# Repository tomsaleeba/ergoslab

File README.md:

> a columnar stagged keyboard that uses a combination of Cherry MX (or
> compatible) and Kailh choc switches to pack in a heap of thumb keys

*Update Dec 2020*: I've been using this keyboard full time (I'm a professional
software developer so it sees a lot of use) for a year now and I'm still in love
with it. If you're considering making one, I would call this design battle
proven now.

*Update Jan 2022*: Still using this full-time and loving it 💪.

- [What is this thing?](#what-is-this-thing)
- [Desgin choices:](#desgin-choices)
- [Build guide](#build-guide)
- [Gerbers](#gerbers)
- [Parts list](#parts-list)
  * [Parts you'll have to find yourself](#parts-youll-have-to-find-yourself)
  * [Parts available with PCB order](#parts-available-with-pcb-order)
- [Developers/contributing](#developerscontributing)
  * [Generating 3 layers of sandwich case](#generating-3-layers-of-sandwich-case)
  * [Generating gerbers](#generating-gerbers)
- [Credit for Kicad symbols/footprints](#credit-for-kicad-symbolsfootprints)
- [FAQ](#faq)

# What is this thing?
Before swapping to this keyboard, I had been using an ErgoDox Infinity and an EZ
as my daily drivers for quite a few years. I loved using them but I was looking
for something more compact and with more (easily accessible) thumb keys. There
are so many candidates
([here](https://docs.google.com/spreadsheets/d/19-rTWbp8SCKdZFByPZu3RT8NSF8vVddDe8WL6R6b1qQ/edit?usp=sharing),
[here](https://keebfol.io/), [here](https://golem.hu/boards/) and
[here](https://github.com/diimdeep/awesome-split-keyboards)) but none match
*exactly* what I want, so I decided build my own!

# Desgin choices:
  - Kailh hotswap sockets for all the MX-style switches (choc are soldered in)
  - ErgoDox style ortho-columnar but with the extra little finger offset of the
      [Diverge 3](https://unikeyboard.io/product/diverge-3/)
  - Make all thumb keys easily accessible from the normal hand position
  - keys for vim-style arrows on the right hand, and directly below the home row
  - same plate design for both halves
  - compatible with QMK firmware, see [keyboard directory in QMK](https://github.com/qmk/qmk_firmware/tree/master/keyboards/ergoslab)
  - optional top LED for layer status ([example](./misc/layer-led-in-action.jpg))
  - optional underglow LEDs
  - minimise overall footprint by using internal standoffs (thanks for the idea
      [ErgoTravel](https://github.com/jpconstantineau/ErgoTravel))
  - use only 1U key caps to minimise size and because stabilisers are annoying
  - author a single "master" PCB and use a python script to generate the 3
      layers of the sandwich case. Makes life much easier to keep them all in
      sync. (See further down for more info)
  - support 5-pin/PCB mount switches

# Build guide
See the [guide here](./build-guide.md).

# Gerbers
See the [releases](https://github.com/tomsaleeba/ergoslab/releases) for this
GitHub repo for the generated Gerber files. You probably want the most recent
version.

If you need to generate your own gerbers, see [how to turn the master PCB into
the 3 generated PCBs](#generating-3-layers-of-sandwich-case) and then [how to
generate gerbers](#generating-gerbers).

# Parts list
## Parts you'll have to find yourself
  - 2x top PCBs (optional if you're happy with PCB mount; untested)
  - 2x middle PCBs (or 4x as they can also be used as the base)
  - 2x base PCBs (if you didn't order 4x middle)
  - 2x Pro Micros
  - 1x TRRS cable
  - 42x Cherry MX (or compatible) switches
  - 42x [Kailh hotswap PCB sockets](https://www.kailhswitch.com/mechanical-keyboard-switches/box-switches/mechanical-keyboard-switches-kailh-pcb-socket.html)
  - 10x Kailh choc switches
  - 42x 1U MX key caps
  - 10x 1U Kailh choc key caps
  - (optional) 2x WS2812 LED from a 144 LEDs/m strip, for layer status lights
  - (optional) more WS2812 LEDs, of any density per meter strip, for underglow
      lighting. 12x is probably a sane number but if you want to run them at
      lower power, you could probably use more.
  - 4x 15mm M2 standoffs (2 per side), for mounting the OLED/ProMicro acrylic cover
  - 8x M2 screws, between 4 and 8mm long, for the above standoffs
  - (optional) 1 or 2 OLED screens
  - 36x M2x4 screw (See Note1 and Note2) for mounting the middle/PCB layer to the base
      plate

**Note1**: the screw/bolt length depends on the height of the standoffs you get.
You want 1.6mm thick PCBs so make sure you don't have *too much* thread on your
screws.

**Note2**: it's highly recommended to get hex head/allen key/ISO7380 screws (see
image below). This is because a phillips head screwdriver probably won't fit
through the holes in the switch plate to tighten the screws on the middle/PCB
layer. You can always drill those holes a bit bigger or loctite the screws in
(so they won't need tighening) to workaround this. As you have hotswap sockets,
you may be able to remove the switches and pull the middle/PCB layer screws out
through the switch holes.  Beware: with 4mm long screws, I couldn't achieve
this, though it was very close.

## Parts available with PCB order
These are the parts you can order from LCSC at the same time as having your PCBs
manufactured. The listed quantity is to assemble *both halves*.

| QTY |  Description                       |  LCSC Part No |
| :---: | :--- | :---: |
|0/2/4| 4.7KO (4701) ±1% (2 per OLED)      |  [C58678](https://lcsc.com/product-detail/Metal-Film-Resistor-TH_4-7KR-4701-1_C58678.html) |
| 2  |  PJ-3200B-4A TRRS Connector         |  [C136687](https://lcsc.com/product-detail/Audio-Video-Connectors_Korean-Hroparts-Elec-PJ-3200B-4A_C136687.html) |
| 2  |  Switch 5.2*5.2*1.5 reset switch    |  [C92584](https://lcsc.com/product-detail/Tactile-Switches_Switch-5-2-5-2-1-5-250gf-Copper-head_C92584.html) |
| 2  |  2.54mm 1*40P round Female header   |  [C9811](https://lcsc.com/product-detail/Female-Header_2-54mm-1-40P-round-Female-header_C9811.html) |
|0/1/2|  OLED Female header                |  [C124413](https://lcsc.com/product-detail/Pin-Header-Female-Header_Ckmtw-Shenzhen-Cankemeng-C124413_C124413.html) |
| 52 |  1N4148 Switching Diode             |  [C14516](https://lcsc.com/product-detail/Switching-Diode_1N4148_C14516.html) |
| 18 |  M2x6mm standoffs (See Note3) for middle/PCB layer to base plate mounting |  [M2x6](https://lcsc.com/product-detail/Studs_Made-in-China-Made-in-China-M2-6-3-5_C193468.html) |

**Note3**: the standoffs between the middle/PCB layer and the base plate can be
quite small, probably as small as 3mm. The problem with that is making sure the
bolts engage the threads enough. Feel free to experiment with getting a super
slim keyboard. Perhaps use a long bolt, a threadless spacer and a nut?

# Developers/contributing
Contributions are welcome. I'm not selling these keyboards and I already have
two for myself so I can't afford to manfacture more PCBs to test changes. If you
make changes to the PCB design, ideally you would confirm it all works by
manufacturing your own PCBs.

Steps for contributing:

1. if it's a non-trival change, consider opening an issue on this repo to talk
   about the change before spending effort
1. fork this repo
1. make your changes
1. if you made a change to the PCB, you need to [regenerate the 3 seperate
   generated PCBs](#generating-3-layers-of-sandwich-case)
1. send a pull request

## Generating 3 layers of sandwich case
We edit a single PCB file that contains the information required to generate all
3 layers (switch plate, circuitry, base) of a sandwich case keyboard. Keeping it
all in one file ensures that things like mounting holes always stay lined up.

There is some magic in the settings of items on the PCB to indicate what layer
they belong on. Read the code for the specifics but as a general guide:
  - we use Eco1.User as the templates for edge cuts that only appear on some
      layers
  - the width of the drawing lines are slightly different so we can determine
      which belongs on each layer
  - the thickness of text is slightly different so we can determine which
      belongs on each layer

You *must* have Kicad installed in your system. Doing this makes the `pcbnew`
python module available. Make sure you don't have any virtualenv, etc activated
as you need to be using you system-wide python. Check for the module by running
the following in the python REPL:

```python
import pcbnew
```

Now you can regenerate the PCBs with:

```bash
python ./generate_pcbs.py
```

Normally keeping generated things in source control is not a good idea but in
the interest of keeping things easy, we include the generated PCBs.

## Generating gerbers
Using KiCad 5.1.4, here's the settings to generate gerbers.

Plot settings (should be the defaults):
```
Plot format: Gerber
Included layers:
  F.Cu
  B.Cu
  F.Paste
  B.Paste
  F.SilkS
  B.SilkS
  F.Mask
  B.Mask
  Edge.Cuts
Plot foorprint values: yes
Plot footprint references: yes
Exclude PCB edge layer from other layers: yes
Exclude pads from silkscreen: yes
Default line width: 0.1mm
Coordinate format: 4.6, unit mm
```

Drill settings:
```
Drill File Format: Excellon
Mirror Y axis: no
Minimal header: no
PTH and NPTH in single file: no
Oval Holes Drill Mode: Use alternate drill mode
Map File Format: PostScript
Drill Origin: Absolute
Drill Units: Inches
Zeros Format: Suppress leading zeros
```

The fix for the JLCPCB PTH layer error was to change the [oval hole drill
mode](https://forum.kicad.info/t/jlcpcb-gives-me-warnings-on-drill-and-edge-cuts/17565/25).

# Credit for Kicad symbols/footprints
- [Kailh reversible footprints](https://github.com/daprice/keyswitches.pretty/blob/f89ef994a51043281f3fa6dfb4a93d8e4bebdbd1/Kailh_socket_reversible.kicad_mod) ([CC BY-SA](https://github.com/daprice/keyswitches.pretty/blob/f89ef994a51043281f3fa6dfb4a93d8e4bebdbd1/LICENSE.md))
- [P-08073 TACT reset switch footprint](https://github.com/kata0510/minisplit/blob/5fc4b23/minisplit-footprint.pretty/TACT_SWITCH_TVBP06.kicad_mod) ([MIT License](https://github.com/kata0510/minisplit/blob/5fc4b233df8120694ade5a3a812970439e8fc585/LICENSE))
- [symbols: TRRS jack, resistor](https://github.com/MakotoKurauchi/helix/tree/master/PCB/beta) (exported from schematic) ([MIT License](https://github.com/MakotoKurauchi/helix/blob/master/LICENSE))
- [LED symbol](https://github.com/tmk/kicad_lib_tmk) (no license)
- 2.54mm pin headers and diode footprints from built in Kicad library
- [footprints: 4 pin TACT reset, ProMicro, diode](https://github.com/jpconstantineau/ErgoTravel/tree/d443bf4/Library/footprints.pretty) ([MIT License](https://github.com/jpconstantineau/ErgoTravel/blob/master/LICENSE))

# FAQ
**How portable is it?**
It weighs 360grams (180grams for each half) with cheap DSA plastic keycaps. It
measures 115mm x 102mm and with 6mm standoffs, it's 16mm to the top of the
switch plate or 31mm to the top of DSA keycaps, including the height of rubber
bump-ons. I'll let you decide how portable you think that is but it was designed
to be portable.

**Is I2C between the halves supported?**
Sort of. The OLED screens use I2C so you won't be able to use them. Also there's
no solder jumpers so you'll have to jump some wires between the OLED header
SDA/SCL pins and the SLAVE_LED pin/data pin on the unused TRRS jack. This isn't
an intended use but you can certainly hack it, check the schematic for details.

**What happened to a single PCB that works as all 3 layers?**
Originally I tried to make one PCB design that works as all 3 layers of a
sandwich design: base, PCB and switch plate. The idea was taken from
[for-split-keyboard](https://github.com/peej/for-split-keyboard) and
[mitosis](https://www.reddit.com/r/MechanicalKeyboards/comments/66588f/wireless_split_qmk_mitosis/).
I failed because I wanted to have minimal post-manufacture cutting by hand and
JLCPCB kept rejecting my desgins as they didn't have strong enough supports to
hold the PCB together though the whole manufacture process. So now we have
"master" PCB design and use a python script to generate the PCBs for each layer
from that master.

**Do you have keyboard-layout-editor source?**\
Yes. Either [this file](./layout.kle) in this repo or here's a (hopefully up to date)
<a href="http://www.keyboard-layout-editor.com/##@@_x:3&t=#000000%0A%0A#115219;&=E%0A%0A#&_x:9.75&t=#000000%0A%0A#115219%0A#9914a6;&=I%0A%0A*%0A%7D;&@_y:-0.875&x:2&t=#000000%0A%0A#115219;&=W%0A%0A/@&_x:1;&=R%0A%0A$&_x:7.75&t=#000000%0A%0A#115219%0A#9914a6;&=U%0A%0A/&%0A%7B&_x:1&t=#000000%0A%0A#115219;&=O%0A%0A';&@_y:-0.875&x:5;&=T%0A%0A%25&_x:5.75;&=Y%0A%0A%5E;&@_y:-0.625&x:1;&=Q%0A%0A!&_x:13.75;&=P%0A%0A%22;&@_y:-0.625&x:3;&=D%0A%0A3&_x:9.75&t=#000000%0A%0A#115219%0A#9914a6;&=K%0A%0A8%0A);&@_y:-0.875&x:2&t=#000000%0A%0A#115219;&=S%0A%0A2&_x:1;&=F%0A%0A4&_x:7.75&t=#000000%0A%0A#115219%0A#9914a6;&=J%0A%0A7%0A(&_x:1&t=#000000%0A%0A#115219;&=L%0A%0A9;&@_y:-0.875&x:5;&=G%0A%0A5&_x:5.75;&=H%0A%0A6;&@_y:-0.625&x:1;&=A%0A%0A1&_x:13.75;&=/:%0A/;%0A0;&@_y:-0.625&x:3&t=#000000%0A#0b458a%0A#115219;&=C%0A%0A+&_x:9.75&t=#000000%0A%0A#115219%0A#9914a6;&=%3C%0A,%0A%0A%5D;&@_y:-0.875&x:2&t=#000000%0A#0b458a%0A#115219;&=X%0A%0A-&_x:1;&=V%0A%0A/=&_x:7.75&t=#000000%0A%0A#115219%0A#9914a6;&=M%0A%0A~%0A%5B&_x:1&t=#000000;&=%3E%0A.;&@_y:-0.875&x:5&t=#000000%0A%0A#115219;&=B%0A%0A%60&_x:5.75;&=N%0A%0A/:;&@_y:-0.625&x:1&t=#000000%0A#0b458a%0A#115219;&=Z%0A%0A/_&_x:13.75&t=#000000;&=?%0A//;&@_y:-0.625&x:3;&=Del&_x:9.75&t=#000000%0A%0A%0A#9914a6;&=%0A%0A%0A%3E%0A%0A%0A%0A%0A%0A%E2%86%93;&@_y:-0.875&x:2&t=#000000;&=Alt&_x:1;&=GUI%0AEnter&_x:7.75&t=#000000%0A%0A%0A#9914a6;&=%0A%0A%0A%3C%0A%0A%0A%0A%0A%0A%E2%86%90&_x:1&t=#000000&a:7;&=%E2%86%91;&@_y:-0.875&x:5&a:4;&=Shift&=Ctrl&_x:3.75&t=#115219;&=Numb%0AEnter&_t=#000000;&=Space;&@_y:-0.625&x:1;&=Leader&_x:13.75&a:7;&=%E2%86%92;&@_y:-0.375&x:2;&=&_a:4;&=Swap&_t=#000000%0A#0b458a;&=Esc&_t=#ab0202;&=Media&_t=#9914a6;&=Brkt&_x:3.75&t=#000000;&=Tab&=AltTab&=Bspc&=Swap&_a:7;&=">permalink</a>

**Do you have a vector of the right hand "plate"?**\
Yep, see [misc/ergoslab-right.svg](misc/ergoslab-right.svg).

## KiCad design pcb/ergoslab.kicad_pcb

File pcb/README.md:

# What is this?
I'm learning about PCB design, so I can make my own mechanical keyboard. This
is a "hello world" project to test my ideas/goals.

# Goals
- Support for Kailh hotswap sockets (and kailh choc as solder on)
- add thumb keys, actually all keys, are accessible from the "home" hand
    position
- One PCB design that works as all 3 layers of a sandwich design: base, PCB and
    switch plate. Idea taken from [for-split-keyboard](https://github.com/peej/for-split-keyboard)
- a design that can be used for either side of a split keyboard
- support 5 pin switches
- single socket for ProMicro. Just mount it flipped for other side
- through-hole diodes, because they're easier to solder
- no RGB because there's no room and it's not my thing

# TODO
- make the ProMicro section snap-off for top layer. Although, we only need it
    for the OLED so we could have a small snapout window for that and then LEDs
    and reset "just work".
- do we mount the promicro on the top or bottom of the PCB? Top works if we
    have snapoff section but if we don't, we need to use the bottom so we can
    access it
- make the bottom row, where the choc switches go, snap-off so they can use the
    switch plate and still reach the PCB. The bonus is that they'll mount lower
    and get out the way of the next row. MX are 5mm deep, choc are 2.35mm so
    the choc row should drop by 2.65mm. The top of the choc switches will be
    ~5mm above the top of the switchplate for the MX switches.
- do we *need* that blank space for thumbs to rest? No, resting on a switch is
    fine.
- should we support the switch plate or just leave it floating? The bottom of
    the switches will be better at supporting keypresses than the switch plate
    so the plate is just for alignment. We need 3.5mm spacers (for MX switches)
    if we choose to attach the switch plate to the pcb. Another option is to
    have small through holes on the PCB and switch plate then use left over
    diode legs to solder them together. Then you can either put standoffs
    between the base and PCB, or drill out the PCB and go between the base and
    switchplate.
- make hole to reach reset button if it's not on the snapoff section
- add OLED? (and pull up resistors)
- make sure the ProMicro is set back enough that you could permanently plug a
    flying-lead plug into it (to go to a USB-C breakout board) and not have it
    vulnerable.
- LEDs:
  - do I need resistors? Yes. At full brightness: 82 - 100ohm for blue, green or white; and 150 - 180ohms for red or yellow
  - add layer status LED footprints
  - can we cut 3mm mounting holes just to the side of the pads and bend the
      LED legs to reach the pads. Means less drilling for us. These need to be
      on the main section, not the snapoff
  - make sure we don't exceed max current for pin groups (100mA). I don't think
      the switches use much current so we should be ok
  - can I drive 3 LEDs with only two pins?
  - can I use a short (3 LEDs) WS2812B strip on the top for layer status?
      The issue is that the OLED uses I2C and (I'm assuming) the LED strip does
      too so if we can have separate code on the master and the slave, we can
      have OLED on one side and layer status on the other. Maybe even just one
      LED as we have lots of different colours.
  - pulling from previous item: do WS2812B strips use I2C or can we drive it
      from any old pin on the PM?
- look at copying how Lily58 lays out the promicro area: https://github.com/kata0510/Lily58
- add solder pads for missing switches, and diodes, so people can make external mounts and
    use them
- add fuses/overcurrent/reverse polarity protection for TRRS? Not sure what
    that coupler solder pad setup on the helix is for
- add licence to repo and silk screen
- add ICSP headers
- add other test points (VCC, RAW, etc)
- do I have the right diode (and footprint)?
- add build instructions to silk screen
- add holes for acrylic cover over oled
- are the PTH for the choc switches going to be a problem as they're over the
    solder on pads for the 1511 socket?
- layout keys as columnar staggered: 0, +1/4 (4.75mm), +3/8 (7.125mm), +1/4 (4.75mm), +1/8 (2.375mm)
- is the ARM CPU in the Ergodox Infinity the same as the Proton-C? If so, can
    we use that firmware to get split support for a controller with more flash?
- name the board as lilydox? Maybe with a chicken silk screen?
- look at adding separate mounting holes for the switch plate to the pcb. Might
    be able to use bolt and nut and some M2 x 5 x 0.3mm nylon washers. The thin
    washer should give us enough granularity to get the right height. Something
    like [these](http://www.allfastsolutions.com.au/product/40868-nylon-flat-washer-m2-x-5-x-0-3mm).
- look at making the outer columns snapoff. We can fit 0.8mm cuts between the
    diodes, or just flip col1 so the diodes are on the inside and we'll have
    heaps of room. Need to add extra mounting holes in between col 1 and 2. All
    depends on being able to live with control and shift under thumbs.
- I think the dimensions are on the silkscreen. If so, move them elsewhere.
- Do I want to make the little finger column drop lower, like the Mitosis
    keyboard? I'd have to sacrifice the row 5 key under it to keep the smaller
    footprint but that's fine because I don't know what I'd use that key for
    anyway.

# Images

# Parts
- 2x PJ-3200B-4A [link](https://lcsc.com/product-detail/Audio-Video-Connectors_Korean-Hroparts-Elec-PJ-3200B-4A_C136687.html) (PJ-320A is discontinued)

# Credit for Kicad symbols/footprints
- [Kailh reversible footprint](https://github.com/daprice/keyswitches.pretty/blob/master/Kailh_socket_reversible.kicad_mod)
- [P-08073 TACT reset switch footprint](https://github.com/kata0510/minisplit/tree/master/minisplit-footprint.pretty)
- [TRRS jack symbol](https://github.com/MakotoKurauchi/helix/tree/master/PCB/beta) (exported from schematic)
- [TRRS footprint](https://github.com/keebio/Keebio-Parts.pretty/blob/master/TRRS-PJ-320A-dual.kicad_mod)
- [LED symbol](https://github.com/tmk/kicad_lib_tmk)
- LED and diode footprints from built in Kicad library
- [footprints: 4 pin TACT reset, promicro, diode](https://github.com/jpconstantineau/ErgoTravel/tree/master/Library/footprints.pretty)

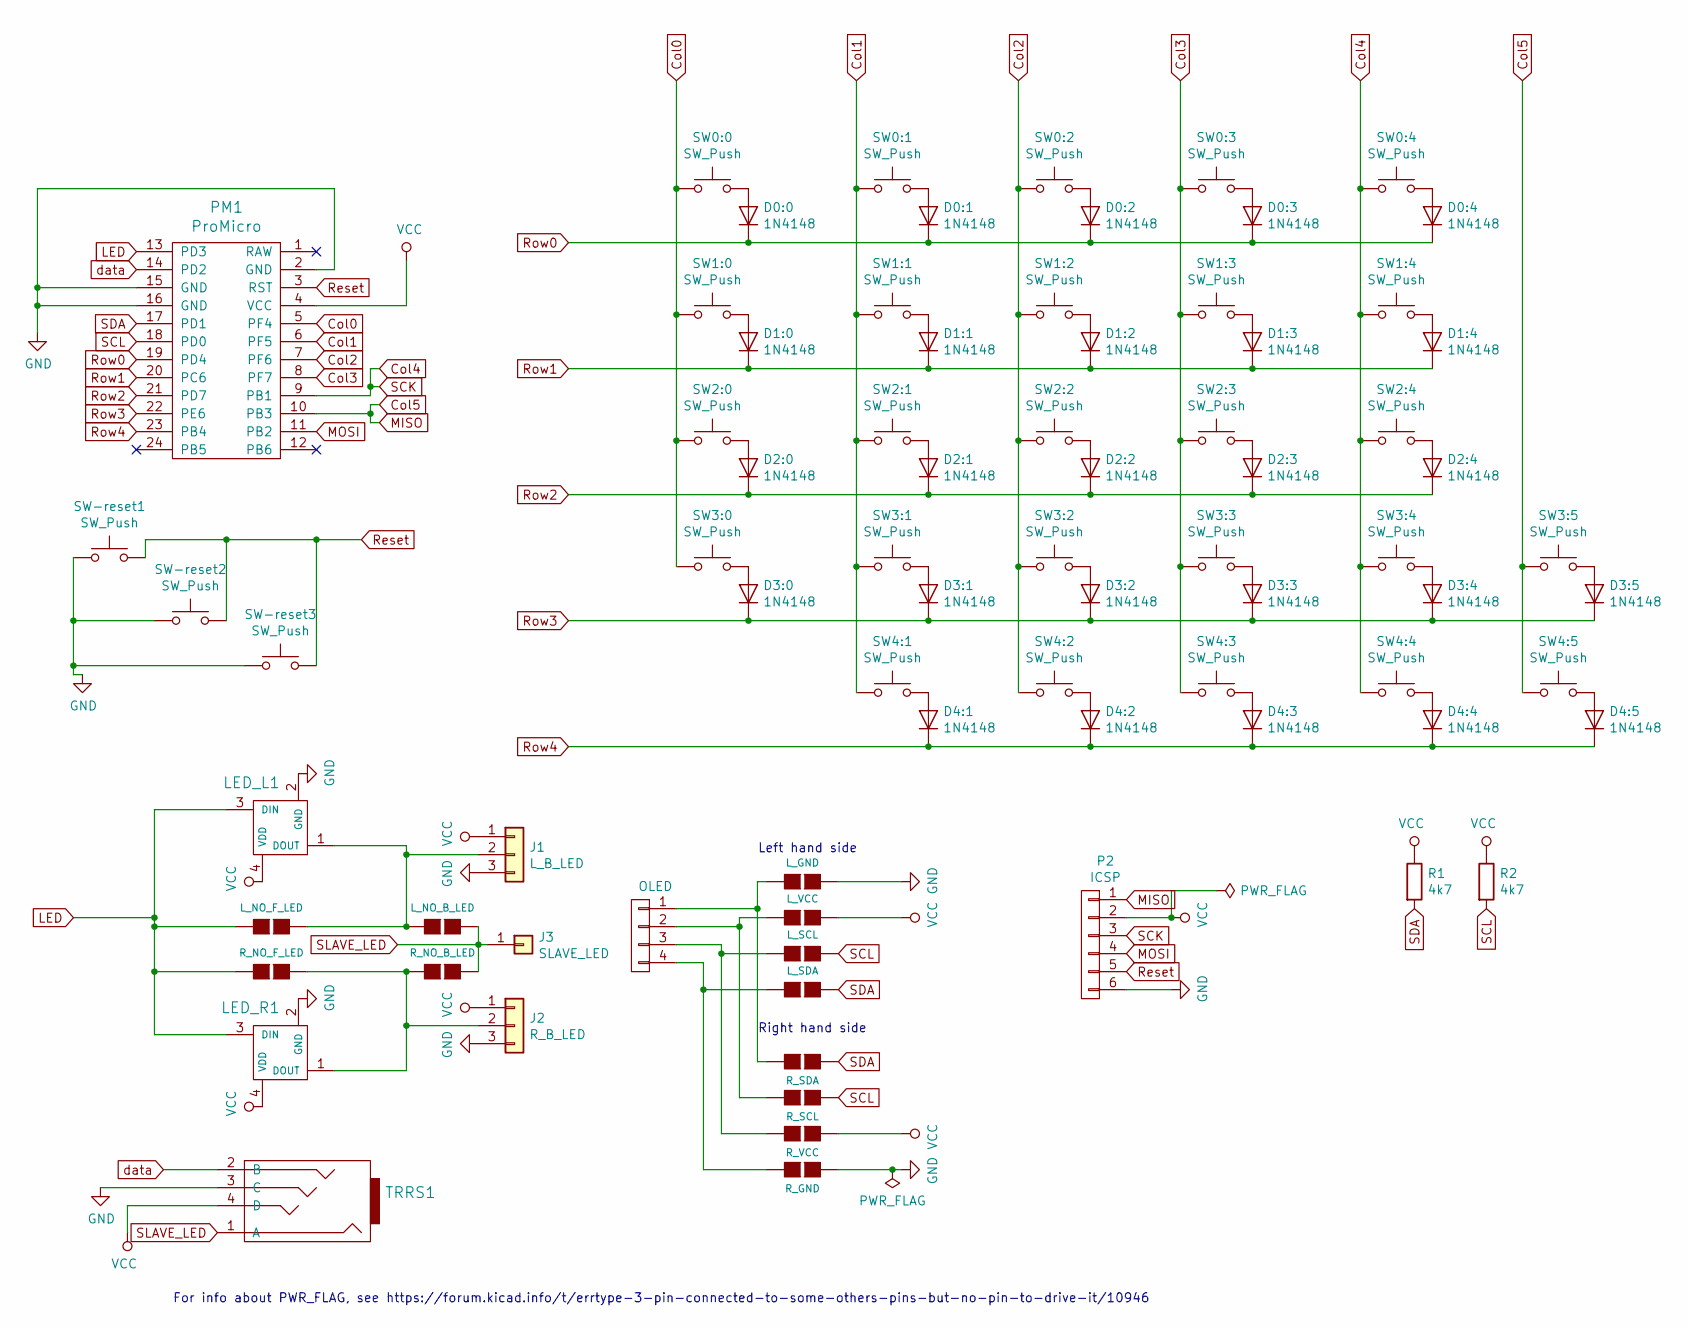
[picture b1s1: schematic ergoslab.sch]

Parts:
D0:0, D0:1, D0:2, D0:3, D0:4, D1:0, D1:1, D1:2, D1:3, D1:4, D2:0, D2:1, D2:2, D2:3, D2:4, D3:0, D3:1, D3:2, D3:3, D3:4, D3:5, D4:1, D4:2, D4:3, D4:4, D4:5: 1N4148; D_DO-35_SOD27_P7.62mm_Horizontal
J1: L_B_LED; ws2812-strip
J2: R_B_LED; ws2812-strip
J3: SLAVE_LED; PinHeader_1x01_P2.54mm_Vertical
JP1: L_GND; Jumper
JP2: L_VCC; Jumper
JP3: L_SCL; Jumper
JP4: L_SDA; Jumper
JP5: R_SDA; Jumper
JP6: R_SCL; Jumper
JP7: R_VCC; Jumper
JP8: R_GND; Jumper
JP9: L_NO_F_LED; Jumper
JP10: L_NO_B_LED; Jumper
JP11: R_NO_B_LED; Jumper
JP12: R_NO_F_LED; Jumper
LED_L1: SK6812mini; ws2812-single
LED_R1: SK6812mini; ws2812-single
P1: OLED; oled_header_helix
P2: ICSP; PinHeader_1x06_P2.54mm_Vertical
PM1: ProMicro; Pro_Micro_ergotravel
R1, R2: 4k7; resistor
SW0:0, SW0:1, SW0:2, SW0:3, SW0:4, SW1:0, SW1:1, SW1:2, SW1:3, SW1:4, SW2:0, SW2:1, SW2:2, SW2:3, SW2:4, SW3:0, SW3:1, SW3:2, SW3:3, SW3:4, SW3:5: SW_Push; Kailh_socket_reversible
SW4:1, SW4:2, SW4:3, SW4:4, SW4:5: SW_Push; kailh-choc-solder-reversible
SW-reset1: SW_Push; TACT_SWITCH_TVBP06
SW-reset2, SW-reset3: SW_Push; SW_TACT_ALPS_SKQGABE010
TRRS1: MJ-4PP-9; TRRS-helix

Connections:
Col0: PM1.5 (PF4), SW0:0.1, SW1:0.1, SW2:0.1, SW3:0.1
Col1: PM1.6 (PF5), SW0:1.1, SW1:1.1, SW2:1.1, SW3:1.1, SW4:1.1
Col2: PM1.7 (PF6), SW0:2.1, SW1:2.1, SW2:2.1, SW3:2.1, SW4:2.1
Col3: PM1.8 (PF7), SW0:3.1, SW1:3.1, SW2:3.1, SW3:3.1, SW4:3.1
Col4: P2.3, PM1.9 (PB1), SW0:4.1, SW1:4.1, SW2:4.1, SW3:4.1, SW4:4.1
Col5: P2.1, PM1.10 (PB3), SW3:5.1, SW4:5.1
GND: J1.3, J2.3, JP1.1 (G1), JP8.1 (G1), LED_L1.2 (GND), LED_R1.2 (GND), P2.6, PM1.2 (GND), PM1.15 (GND), PM1.16 (GND), SW-reset1.1, SW-reset2.1, SW-reset3.1, TRRS1.3 (C)
LED: JP9.2 (G2), JP12.2 (G2), LED_L1.3 (DIN), LED_R1.3 (DIN), PM1.13 (PD3)
MOSI: P2.4, PM1.11 (PB2)
unnamed: D0:0.2 (A), SW0:0.2
unnamed: D0:1.2 (A), SW0:1.2
unnamed: D0:2.2 (A), SW0:2.2
unnamed: D0:3.2 (A), SW0:3.2
unnamed: D0:4.2 (A), SW0:4.2
unnamed: D1:0.2 (A), SW1:0.2
unnamed: D1:1.2 (A), SW1:1.2
unnamed: D1:2.2 (A), SW1:2.2
unnamed: D1:3.2 (A), SW1:3.2
unnamed: D1:4.2 (A), SW1:4.2
unnamed: D2:0.2 (A), SW2:0.2
unnamed: D2:1.2 (A), SW2:1.2
unnamed: D2:2.2 (A), SW2:2.2
unnamed: D2:3.2 (A), SW2:3.2
unnamed: D2:4.2 (A), SW2:4.2
unnamed: D3:0.2 (A), SW3:0.2
unnamed: D3:1.2 (A), SW3:1.2
unnamed: D3:2.2 (A), SW3:2.2
unnamed: D3:3.2 (A), SW3:3.2
unnamed: D3:4.2 (A), SW3:4.2
unnamed: D3:5.2 (A), SW3:5.2
unnamed: D4:1.2 (A), SW4:1.2
unnamed: D4:2.2 (A), SW4:2.2
unnamed: D4:3.2 (A), SW4:3.2
unnamed: D4:4.2 (A), SW4:4.2
unnamed: D4:5.2 (A), SW4:5.2
unnamed: J1.2, JP9.1 (G1), JP10.2 (G2), LED_L1.1 (DOUT)
unnamed: J2.2, JP11.2 (G2), JP12.1 (G1), LED_R1.1 (DOUT)
unnamed: JP1.2 (G2), JP5.2 (G2), P1.1
unnamed: JP2.2 (G2), JP6.2 (G2), P1.2
unnamed: JP3.2 (G2), JP7.2 (G2), P1.3
unnamed: JP4.2 (G2), JP8.2 (G2), P1.4
Reset: P2.5, PM1.3 (RST), SW-reset1.2, SW-reset2.2, SW-reset3.2
Row0: D0:0.1 (K), D0:1.1 (K), D0:2.1 (K), D0:3.1 (K), D0:4.1 (K), PM1.19 (PD4)
Row1: D1:0.1 (K), D1:1.1 (K), D1:2.1 (K), D1:3.1 (K), D1:4.1 (K), PM1.20 (PC6)
Row2: D2:0.1 (K), D2:1.1 (K), D2:2.1 (K), D2:3.1 (K), D2:4.1 (K), PM1.21 (PD7)
Row3: D3:0.1 (K), D3:1.1 (K), D3:2.1 (K), D3:3.1 (K), D3:4.1 (K), D3:5.1 (K), PM1.22 (PE6)
Row4: D4:1.1 (K), D4:2.1 (K), D4:3.1 (K), D4:4.1 (K), D4:5.1 (K), PM1.23 (PB4)
SCL: JP3.1 (G1), JP6.1 (G1), PM1.18 (PD0), R2.2
SDA: JP4.1 (G1), JP5.1 (G1), PM1.17 (PD1), R1.2
SLAVE_LED: J3.1, JP10.1 (G1), JP11.1 (G1), TRRS1.1 (A)
VCC: J1.1, J2.1, JP2.1 (G1), JP7.1 (G1), LED_L1.4 (VDD), LED_R1.4 (VDD), P2.2, PM1.4 (VCC), R1.1, R2.1, TRRS1.4 (D)
data: PM1.14 (PD2), TRRS1.2 (B)

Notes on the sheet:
Right hand side
Left hand side
For info about PWR_FLAG, see https://forum.kicad.info/t/errtype-3-pin-connected-to-some-others-pins-but-no-pin-to-drive-it/10946

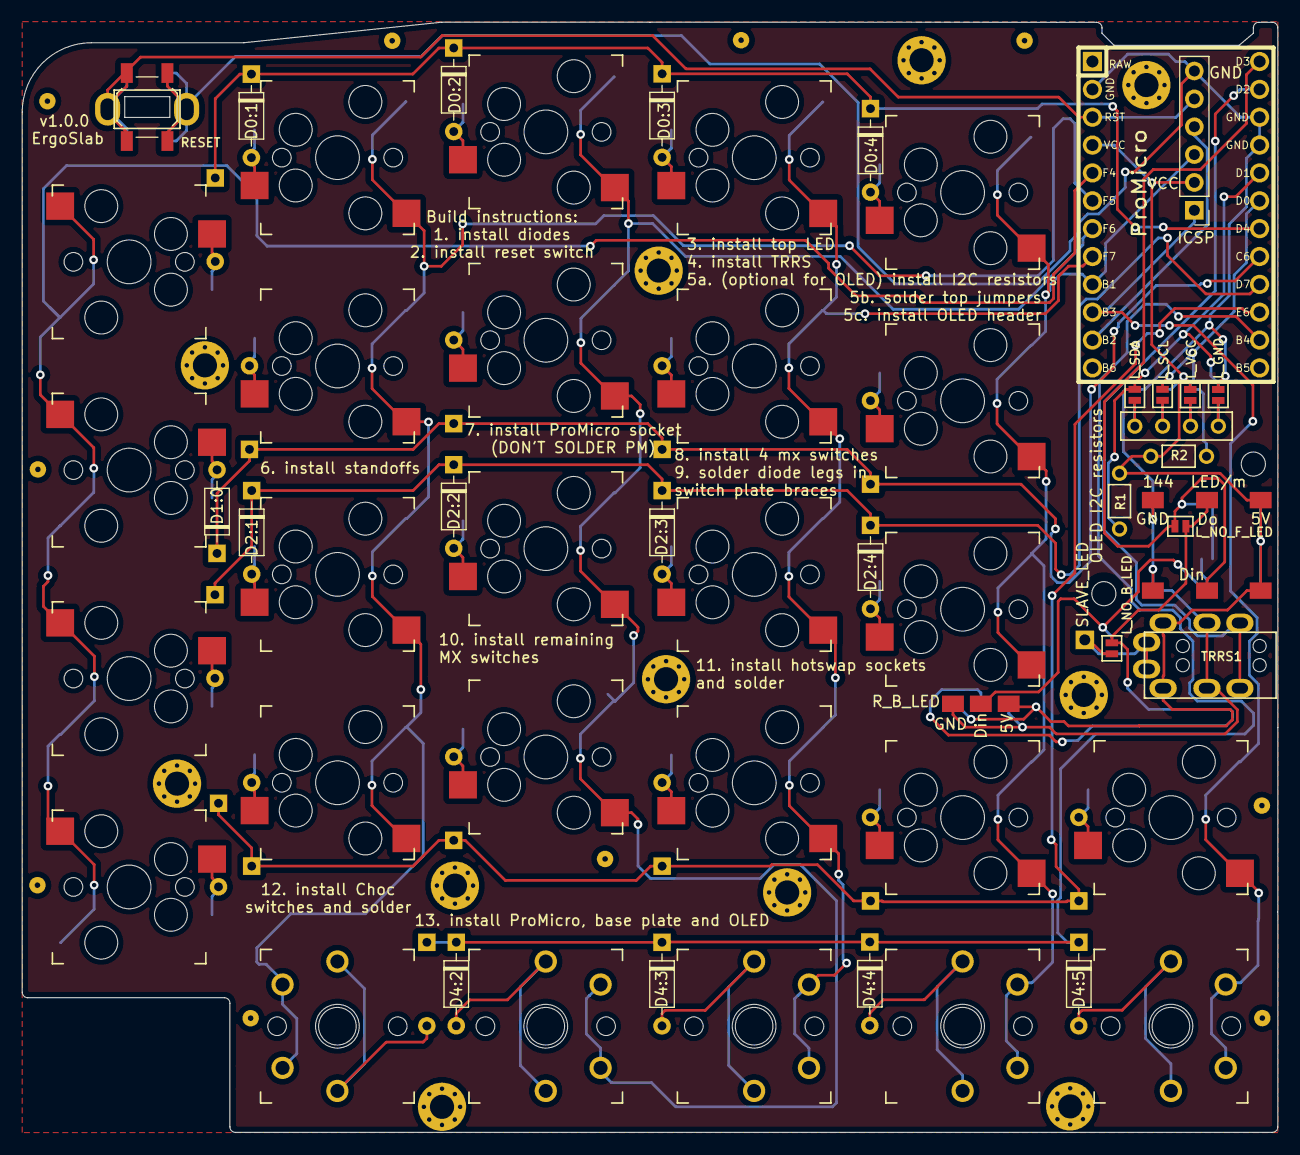
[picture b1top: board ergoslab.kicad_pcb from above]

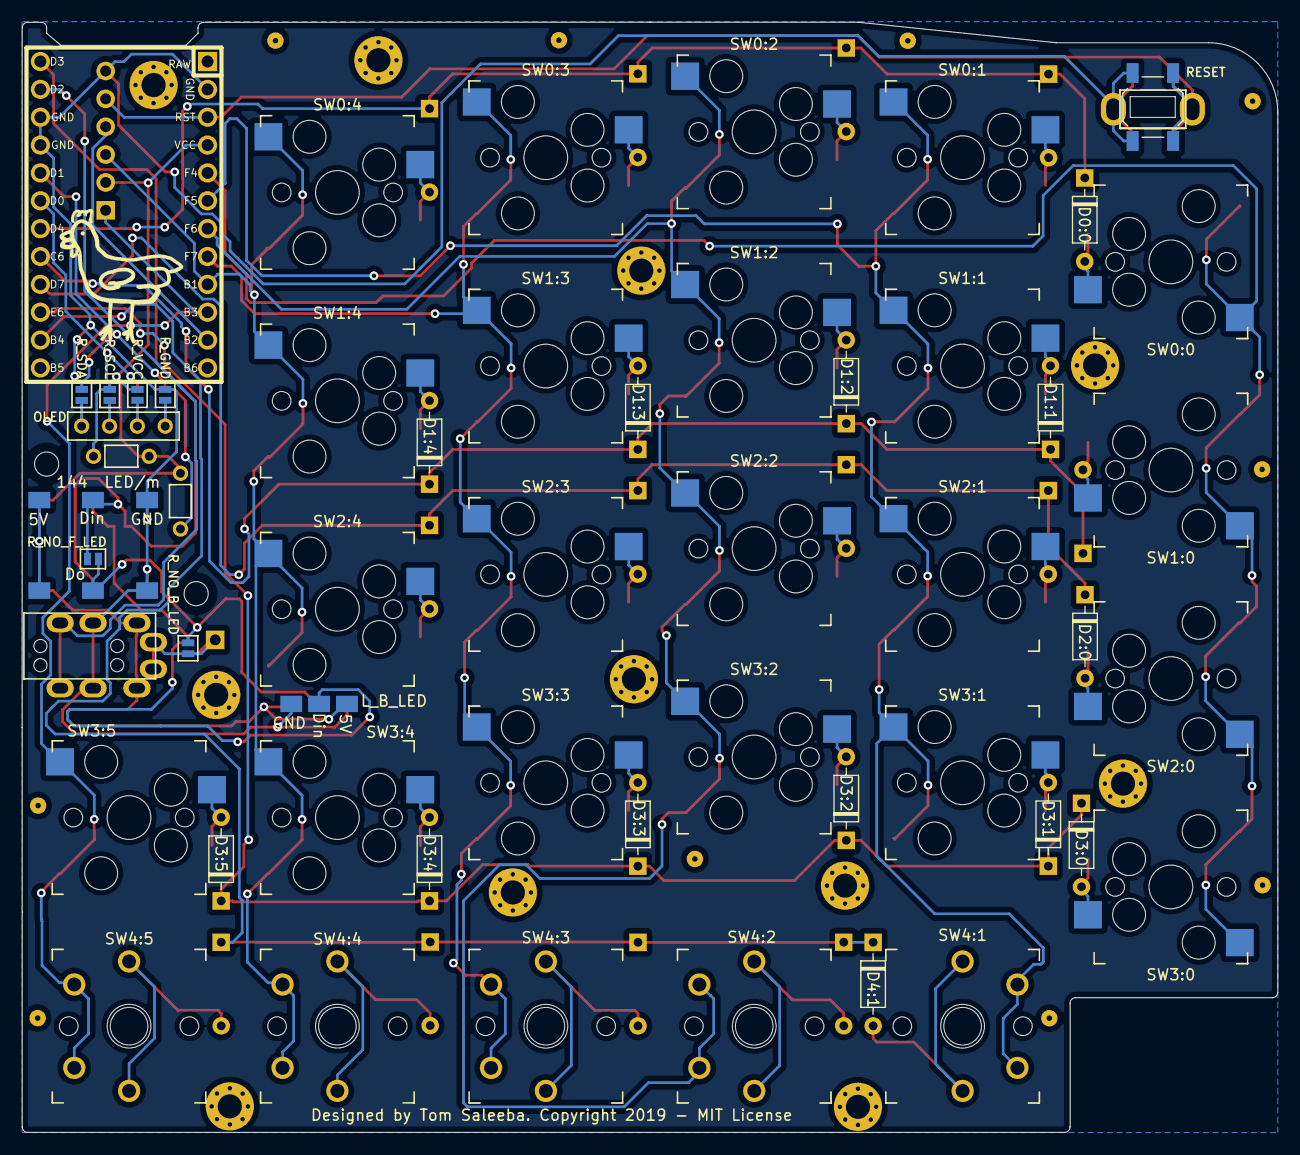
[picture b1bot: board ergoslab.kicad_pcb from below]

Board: 2 copper layers, 114.5 x 101.2 mm, 102 parts (24 on the bottom side), 52 nets.

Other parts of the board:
Brace0, Brace1, Brace2, Brace3, Brace4, Brace5, Brace6, Brace7: switchplate-brace
BraceNotTop0, BraceNotTop1: switchplate-brace
CHICKEN: LOGO; chicken
Mount0, Mount1, Mount2, Mount3, Mount4, Mount5, Mount6, Mount7: MountingHole_2.2mm_M2_Pad_Via
MountNotTop0, MountNotTop3, MountNotTop4: MountingHole_2.2mm_M2_Pad_Via
MountNotTop1, MountNotTop2: VAL**; HOLE_M2

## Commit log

2019-10-05 docs: add parts list
2019-10-05 docs: mention method for using optional switch holes
2019-10-05 docs: update parts list
2019-10-05 docs: add more links
2019-10-05 docs: add links to lists of existing keyboards
2019-10-14 docs: add link to another keyboard list
2019-10-15 feat: remove seventh column of keys from main block and bring pro micro in closer
2019-10-16 docs: add question about IO expander
2019-10-17 docs: update questions
2019-10-22 feat: adjust thumb keys slighty to give more access to the middle one
2019-10-25 docs: add another link to a keyboard list
2019-10-27 chore: add POC, basic PCB
2019-10-27 chore: enlarged schematic to 4x4, fixed middle layer hole issue. Making a checkpoint before I try to get the netlist to update without destroying all my existing stuff
2019-10-27 chore: fixing some of the associations between the schema and pcb design. Still more to go
2019-10-28 docs: add todo list to test PCB
2019-10-28 docs: more stuff
2019-10-28 feat: add reset switch and TRRS connector, test making promicro snapoff
2019-10-28 docs: add TACT switch part number
2019-10-28 docs: add link to Lily58
2019-10-28 feat: add all switches and LEDs to schematic
2019-10-29 fix: add idea for switch footprint that support choc solder in
2019-10-29 fix: get TRRS schematic to line up with footprint
2019-10-29 feat: more playing with layout
2019-10-30 docs: update todo list
2019-10-30 chore: add some 4 pin reset switches, played with new footprints
2019-10-30 chore: add throwing star thumb tester
2019-10-30 chore: add throwing star thumb tester DXF
2019-10-30 chore: revise throwing star layout, add helix stagger layout
2019-10-31 feat: remove footprint with solder on for fullsize MX switches, that wasn't ever going to work; fix existing combo footprint to add clearance for choc switches, start the col stagger layout
2019-10-31 feat: complete key layout
2019-10-31 chore: tidy up PCB, still lots of errors
2019-11-03 chore: fix misaligned edge cuts, remove some dupe components
2019-11-03 feat: some more layout
2019-11-05 docs: update todo list, add reference images
2019-11-06 feat: add perforations to pcb
2019-11-07 feat: try out moving left edge diodes to inner, tidy up edge cuts of bottom row, add edge connectors for moving thumb switch
2019-11-08 flipped left edge diodes, shrunk board a bit
2019-11-08 chore: add 100mm measurements
2019-11-09 feat: name all switches and diodes on PCB, still need to update refs
2019-11-10 feat: add all footprint refs, update netlist, do some wiring
2019-11-11 feat: wire up edge connectors
2019-11-11 feat: attempt to make usb-c breakout board footprint
2019-11-12 feat: another attempt at layout with the usb-c breakout board
2019-11-13 feat: add OLED and iCSP to schematic
2019-11-14 fix: updates related to copying helix underglow
2019-11-14 feat: updated test layouts
2019-11-14 feat: add new test layout
2019-11-15 chore: add dimension to the PCB to check something
2019-11-19 docs: update readme
2019-11-23 feat: add add new test layout with more little finger offset
2019-11-26 feat: move to new 5 col version
2019-11-29 feat: lots done, still need more LEDs, the I2C resistors and finish the traces
2019-11-30 feat: fully wired but stuff one side of the oled panels
2019-11-30 feat: fill in zones, add instructions, correct OLED jumpers on right(bottom), still need to finalise LED wiring
2019-12-02 fix: undo some wrong decisions with the LEDs
2019-12-02 fix: correct (I think) the LED wiring
2019-12-03 feat: create a choc-only footprint and use that for the bottom row, check that making the other switches MX only will remove DRC errors and it will, so that needs to be done. Also add choc reference 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
2019-12-03 feat: add back LED bypass jumpers
2019-12-03 feat: update all MX switches to MX-only footprint, still need to update edge cuts
2019-12-03 refactor: remove old stuff we don't need, move the PCB up, still more house keeping to go
2019-12-03 docs: fix permalink in readme
2019-12-04 fix: update edge cuts for MX switches, refresh PCB render
2019-12-04 docs: tidy up README, start build guide
2019-12-05 refactor: house clean unused symbols and footprints, merge all symbols into one library, rename kicad project from testy to ergoslab
2019-12-05 feat: update chicken
2019-12-05 fix: update single WS2812 footprint to be the correct size, still need to update the PCB
2019-12-06 docs: add list of parts to order
2019-12-06 chore: tidy readme
2019-12-06 fix: update single WS2812 footprint on PCB, had to expand space allocated for ProMicro
2019-12-06 fix: move dimensions off silk screen, change version 1.0=>0.1.0
2019-12-06 chore: update zone fills
2019-12-10 docs: update readme with settings for generating gerbers
2019-12-11 fix: increase all snap-off supports to at least 3mm as per JLCPCB requirements
2019-12-11 docs: add link to gerbers from README
2019-12-11 fix: test making switch plate cutout the correct size on SW4:4
2019-12-11 fix: make switchplate cutout for SW4:4 this time, last commit was actually SW3:4
2019-12-11 fix: make all switchplate cutouts 14mm so switches will actually fit
2019-12-15 chore: add refs for switchplate supports
2019-12-15 feat: start creating python script to generate separate boards from the master board
2019-12-15 fix: make sure edge.cuts remain on base layer, figure out how to read line width in python script
2019-12-18 fix: generating something for all layers, outline is good, zones are refilled, still more to do
2019-12-19 feat: completed the new approach of generating PCBs from the master
2019-12-19 chore: update pcb render
2019-12-19 docs: clarify field name
2019-12-19 docs: clarify required PCBs
2019-12-28 chore: bump version to 1.0.0 now I know it works (typing on it right now), give OLED resistor more space, make choc row M2 mounts more obvious, fix up silk screen build instructions
2019-12-29 docs: update README, add photos to build guide
2019-12-29 docs: fix errors in build guide
2019-12-29 docs: add photo of layer LED in action
2019-12-30 docs: update build guide to talk about how to solder the jumpers
2020-01-02 docs: remove non-sensical idea about making a slim keyboard
2020-01-02 docs: update photo of keyboard now I have pretty new keycaps
2020-01-02 docs: add note about hotswap sockets
2020-01-03 chore: rotate labels on throwing star test layout
2020-01-03 docs: add note about difficulty in getting PCB screw out through switch plate holes
2020-01-11 docs: add 'developers' section to the readme
2020-01-11 docs: add TOC to readme
2020-01-11 docs: fix readme TOC
2020-02-01 partial: writing about how to run the base
2020-06-01 docs: update some README text
2020-12-07 docs: add note about 1 year of use, format some text in README
2020-12-18 chore: add right plate vector for jhelvy/splitKbCompare tool
2020-12-18 docs: format README
2020-12-18 docs: more README fixes
2022-02-03 docs: fix broken link to Kailh socket

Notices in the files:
pcb/ergoslab.kicad_pcb:
Designed by Tom Saleeba. Copyright 2019 - MIT License
